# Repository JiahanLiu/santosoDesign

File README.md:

# santosoDesign

Julia Conger, Jiahan Liu, Joshua Graham, Kassandra Smith, Braden Stotmeister, Madeline Jasper

Suma, Santoso, Oriana, Alvaro, Boom

1) Ensure code compiles before push
2) Update .gitignore for all user dependent files.

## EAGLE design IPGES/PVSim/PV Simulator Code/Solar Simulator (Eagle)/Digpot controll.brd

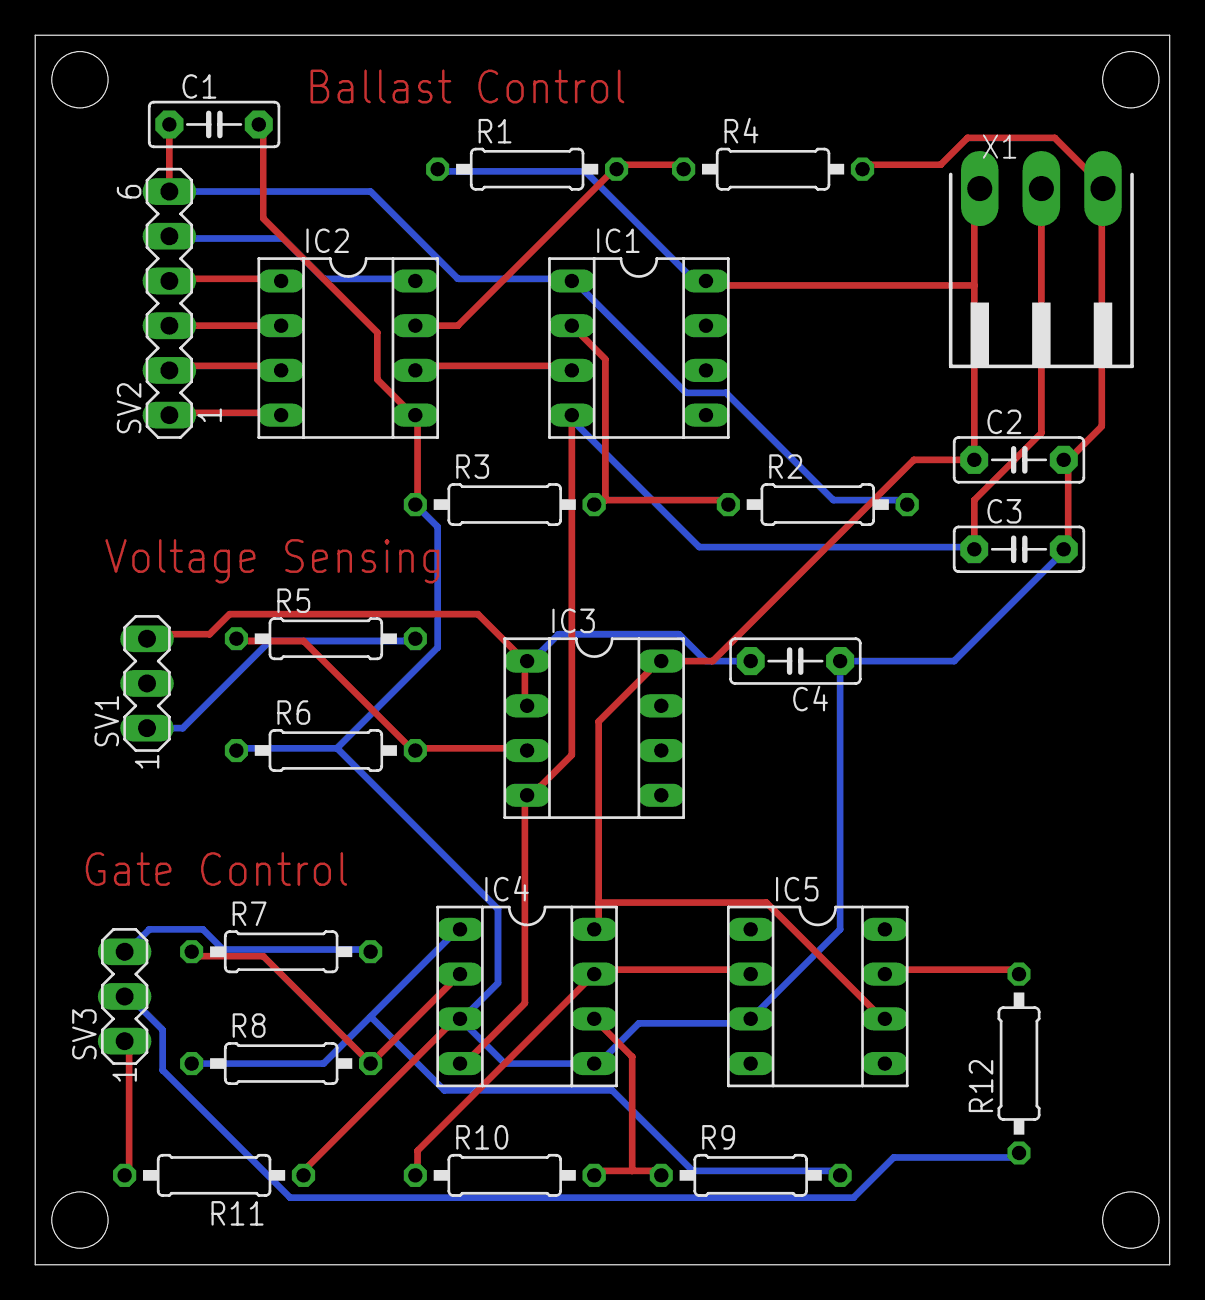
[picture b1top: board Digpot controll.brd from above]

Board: 2 copper layers, 64.4 x 69.8 mm, 25 parts (0 on the bottom side), 23 nets.

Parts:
C1, C2, C3, C4: C5B2.5
IC1, IC2, IC3, IC4, IC5: SOCKET-08
R1, R2, R3, R4, R5, R6, R7, R8, R9, R10, R11, R12: 0207/10
SV1, SV3: MA03-1
SV2: MA06-1
X1: 90-3

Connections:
GND: C1.2, C2.2, C3.2, C4.1, IC2.5, IC4.3, IC4.5, IC5.3, R3.1, R4.2, R6.1, R11.1, X1.3
unnamed: IC1.2, R2.1, R3.2
unnamed: IC1.3, IC2.6
unnamed: IC2.1, SV2.4
unnamed: C1.1, IC1.1, R2.2, SV2.6
unnamed: IC2.7, R1.2, R4.1
unnamed: IC2.2, SV2.3
unnamed: IC2.3, SV2.2
unnamed: IC2.4, SV2.1
unnamed: IC3.3, R5.1, R6.2
unnamed: IC2.8, SV2.5
unnamed: C4.2, IC3.1, IC3.2, SV1.3
unnamed: R5.2, SV1.1
unnamed: R7.2, SV3.3
unnamed: IC4.2, R7.1, R8.2
unnamed: IC4.1, R8.1, R9.2
unnamed: IC4.6, R9.1, R10.2
unnamed: IC4.7, IC5.2, R10.1
unnamed: R11.2, SV3.1
S$1: IC5.7, R12.2
S$2: R12.1, SV3.2
VCC: C2.1, IC1.8, IC3.8, IC4.8, IC5.6, R1.1, X1.1
VSS: C3.1, IC1.4, IC3.4, IC4.4, X1.2

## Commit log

2017-10-11 Add Solar Simulation Python code
2017-10-11 Add Existing Matlab and Simulink Models
2017-10-11 Version 0.0 from Tivaware for freeRTOS
2017-10-11 Update Readme. Good Manners for using this respoistory.
2017-10-11 Restructure files
2017-10-11 Finish Restructure Files
2017-10-11 Compile Updates for Working
2017-10-14 ADC PD3 sequence 4
2017-10-16 Timer Triggered ADC
2017-10-16 4 ADC Inputs
2017-10-16 PWM Working
2017-10-16 Demo for Santoso
2017-10-17 Add MPPT Code from Rungga
2017-11-17 Add WISE code pulled from corrupted SD card
    Update MPPT code
2017-11-29 Chopper with deadband
2017-11-29 Remove WISE and PVSim documents for transfer to separate repositories
2017-11-30 1) Moved non-tm4c stuff into different repo. 2) Interpreter
2017-11-30 Removed Vishay
2018-02-21 initial commit of working python files. Works on RaspPi to simulate solar/wind days simultaneously with real-time simulation graph output.
2018-02-21 updated code to current programs from Py. actually does what first commit says now.
